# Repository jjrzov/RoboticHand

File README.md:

# ME 507 - Teleoperated Robot Hand
By: Sydney Alexander & Jorge Ramirez

This repository holds all the work done for our Fall 2025 ME 507 mechatronics 
class, Mechanical Control System Design. We chose to do a teleoperated
robot hand for our final project. The robot hand is controlled by a glove
that can be worn by the user. The user has control over each finger and a
palm bending motion on the robot hand.

The repository is split into 3 parts: 
* Mechanical Design Files (<https://github.com/jjrzov/RoboticHand/tree/main/CAD>)
* PCB Files
* Software Files    (<https://github.com/jjrzov/RoboticHand/tree/main/Code>)

More information can be found in the report:
<https://docs.google.com/document/d/1OJhpxcHGqPs-KphNlcnnhu6IluXgC120gNegF1xwxDM/edit?usp=sharing>

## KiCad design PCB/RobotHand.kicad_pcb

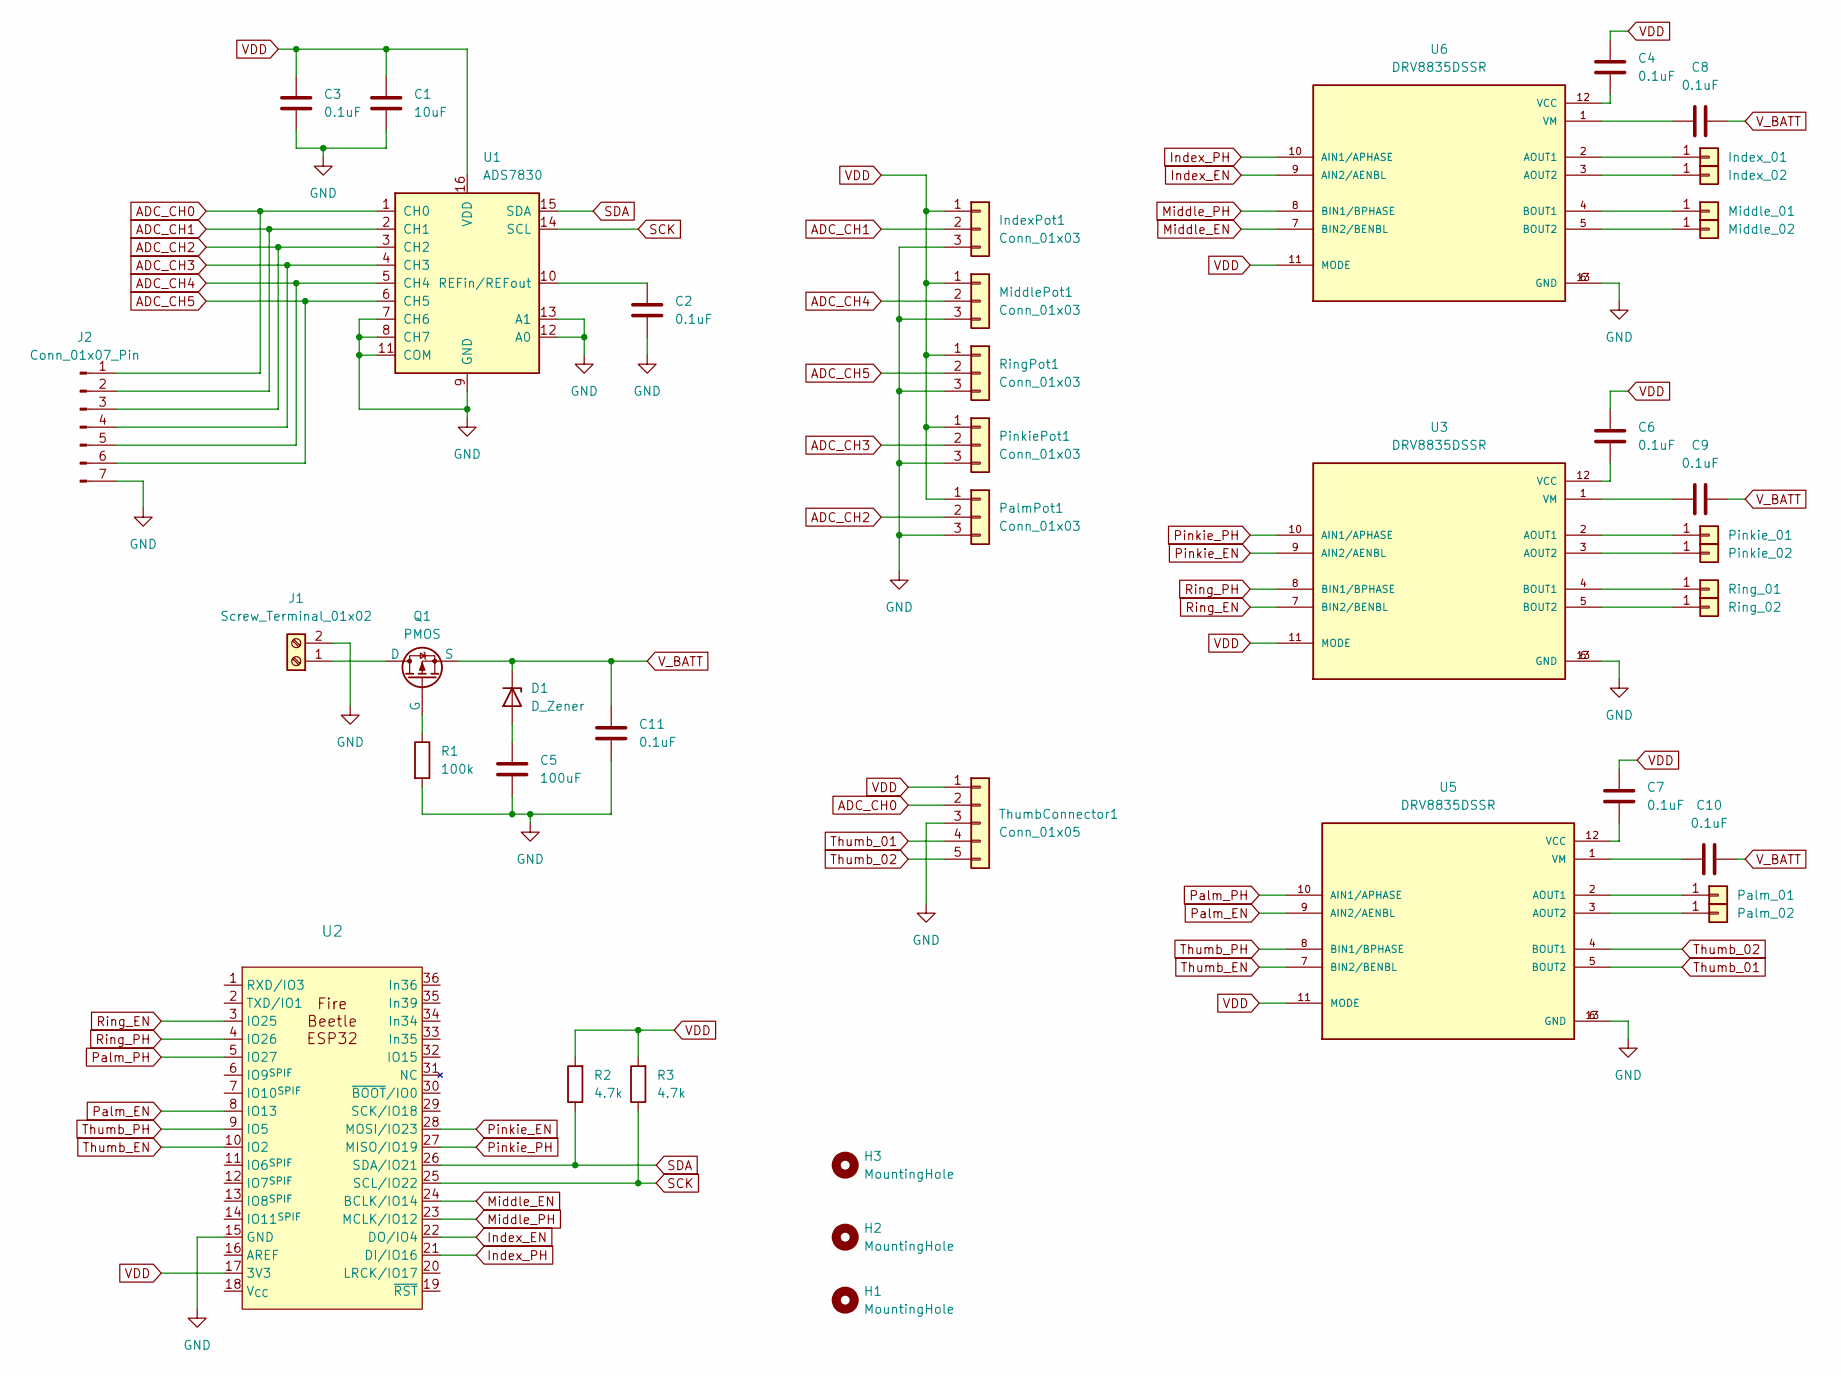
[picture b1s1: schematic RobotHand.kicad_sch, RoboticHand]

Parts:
C1: 10uF; C_0805_2012Metric_Pad1.18x1.45mm_HandSolder
C2, C3, C4, C6, C7, C8, C9, C10, C11: 0.1uF; C_0805_2012Metric_Pad1.18x1.45mm_HandSolder
C5: 100uF; C_0805_2012Metric_Pad1.18x1.45mm_HandSolder
D1: D_Zener; D_SOD-123
H1, H2, H3: MountingHole; MountingHole_6.4mm_M6
IndexPot1: Conn_01x03; PinHeader_1x03_P2.54mm_Vertical
Index_01, Index_02: Conn_01x01; PinHeader_1x01_P2.54mm_Vertical
J1: Screw_Terminal_01x02; TerminalBlock_Xinya_XY308-2.54-2P_1x02_P2.54mm_Horizontal
J2: Conn_01x07_Pin; PinSocket_1x07_P2.54mm_Vertical
MiddlePot1: Conn_01x03; PinHeader_1x03_P2.54mm_Vertical
Middle_01, Middle_02: Conn_01x01; PinHeader_1x01_P2.54mm_Vertical
PalmPot1: Conn_01x03; PinHeader_1x03_P2.54mm_Vertical
Palm_01, Palm_02: Conn_01x01; PinHeader_1x01_P2.54mm_Vertical
PinkiePot1: Conn_01x03; PinHeader_1x03_P2.54mm_Vertical
Pinkie_01, Pinkie_02: Conn_01x01; PinHeader_1x01_P2.54mm_Vertical
Q1: PMOS; SOT-23-3
R1: 100k; R_0805_2012Metric
R2, R3: 4.7k; R_0805_2012Metric
RingPot1: Conn_01x03; PinHeader_1x03_P2.54mm_Vertical
Ring_01, Ring_02: Conn_01x01; PinHeader_1x01_P2.54mm_Vertical
ThumbConnector1: Conn_01x05; PinHeader_1x05_P2.54mm_Vertical
U1: ADS7830; TSSOP-16_4.4x5mm_P0.65mm
U2: FireBeetle-ESP32
U3, U5, U6: DRV8835DSSR; WSON-12-1EP_3x2mm_P0.5mm_EP1x2.65; PARTREV H

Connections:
ADC_CH0: J2.1, ThumbConnector1.2, U1.1 (CH0)
ADC_CH1: IndexPot1.2, J2.2, U1.2 (CH1)
ADC_CH2: J2.3, PalmPot1.2, U1.3 (CH2)
ADC_CH3: J2.4, PinkiePot1.2, U1.4 (CH3)
ADC_CH4: J2.5, MiddlePot1.2, U1.5 (CH4)
ADC_CH5: J2.6, RingPot1.2, U1.6 (CH5)
GND: C1.1, C2.2, C3.2, C5.2, C11.2, IndexPot1.3, J1.2, J2.7, MiddlePot1.3, PalmPot1.3, PinkiePot1.3, R1.2, RingPot1.3, ThumbConnector1.3, U1.7 (CH6), U1.8 (CH7), U1.9 (GND), U1.11 (COM), U1.12 (A0), U1.13 (A1), U2.15 (GND), U3.6 (GND), U3.13 (GND), U5.6 (GND), U5.13 (GND), U6.6 (GND), U6.13 (GND)
Index_EN: U2.22 (DO/IO4), U6.9 (AIN2/AENBL)
Index_PH: U2.21 (DI/IO16), U6.10 (AIN1/APHASE)
Middle_EN: U2.24 (BCLK/IO14), U6.7 (BIN2/BENBL)
Middle_PH: U2.23 (MCLK/IO12), U6.8 (BIN1/BPHASE)
unnamed: C5.1, D1.2 (A)
unnamed: Index_01.1, U6.2 (AOUT1)
unnamed: Index_02.1, U6.3 (AOUT2)
unnamed: J1.1, Q1.1 (D)
unnamed: Middle_01.1, U6.4 (BOUT1)
unnamed: Middle_02.1, U6.5 (BOUT2)
unnamed: Palm_01.1, U5.2 (AOUT1)
unnamed: Palm_02.1, U5.3 (AOUT2)
unnamed: Pinkie_01.1, U3.2 (AOUT1)
unnamed: Pinkie_02.1, U3.3 (AOUT2)
unnamed: Q1.2 (G), R1.1
unnamed: Ring_01.1, U3.4 (BOUT1)
unnamed: Ring_02.1, U3.5 (BOUT2)
unnamed: C2.1, U1.10 (REFin/REFout)
unnamed: C6.1, U3.12 (VCC)
unnamed: C9.1, U3.1 (VM)
unnamed: C7.1, U5.12 (VCC)
unnamed: C10.2, U5.1 (VM)
unnamed: C4.1, U6.12 (VCC)
unnamed: C8.1, U6.1 (VM)
Palm_EN: U2.8 (IO13), U5.9 (AIN2/AENBL)
Palm_PH: U2.5 (IO27), U5.10 (AIN1/APHASE)
Pinkie_EN: U2.28 (MOSI/IO23), U3.9 (AIN2/AENBL)
Pinkie_PH: U2.27 (MISO/IO19), U3.10 (AIN1/APHASE)
Ring_EN: U2.3 (IO25), U3.7 (BIN2/BENBL)
Ring_PH: U2.4 (IO26), U3.8 (BIN1/BPHASE)
SCK: R3.1, U1.14 (SCL), U2.25 (SCL/IO22)
SDA: R2.1, U1.15 (SDA), U2.26 (SDA/IO21)
Thumb_01: ThumbConnector1.4, U5.5 (BOUT2)
Thumb_02: ThumbConnector1.5, U5.4 (BOUT1)
Thumb_EN: U2.10 (IO2), U5.7 (BIN2/BENBL)
Thumb_PH: U2.9 (IO5), U5.8 (BIN1/BPHASE)
VDD: C1.2, C3.1, C4.2, C6.2, C7.2, IndexPot1.1, MiddlePot1.1, PalmPot1.1, PinkiePot1.1, R2.2, R3.2, RingPot1.1, ThumbConnector1.1, U1.16 (VDD), U2.17 (3V3), U3.11 (MODE), U5.11 (MODE), U6.11 (MODE)
V_BATT: C8.2, C9.2, C10.1, C11.1, D1.1 (K), Q1.3 (S)

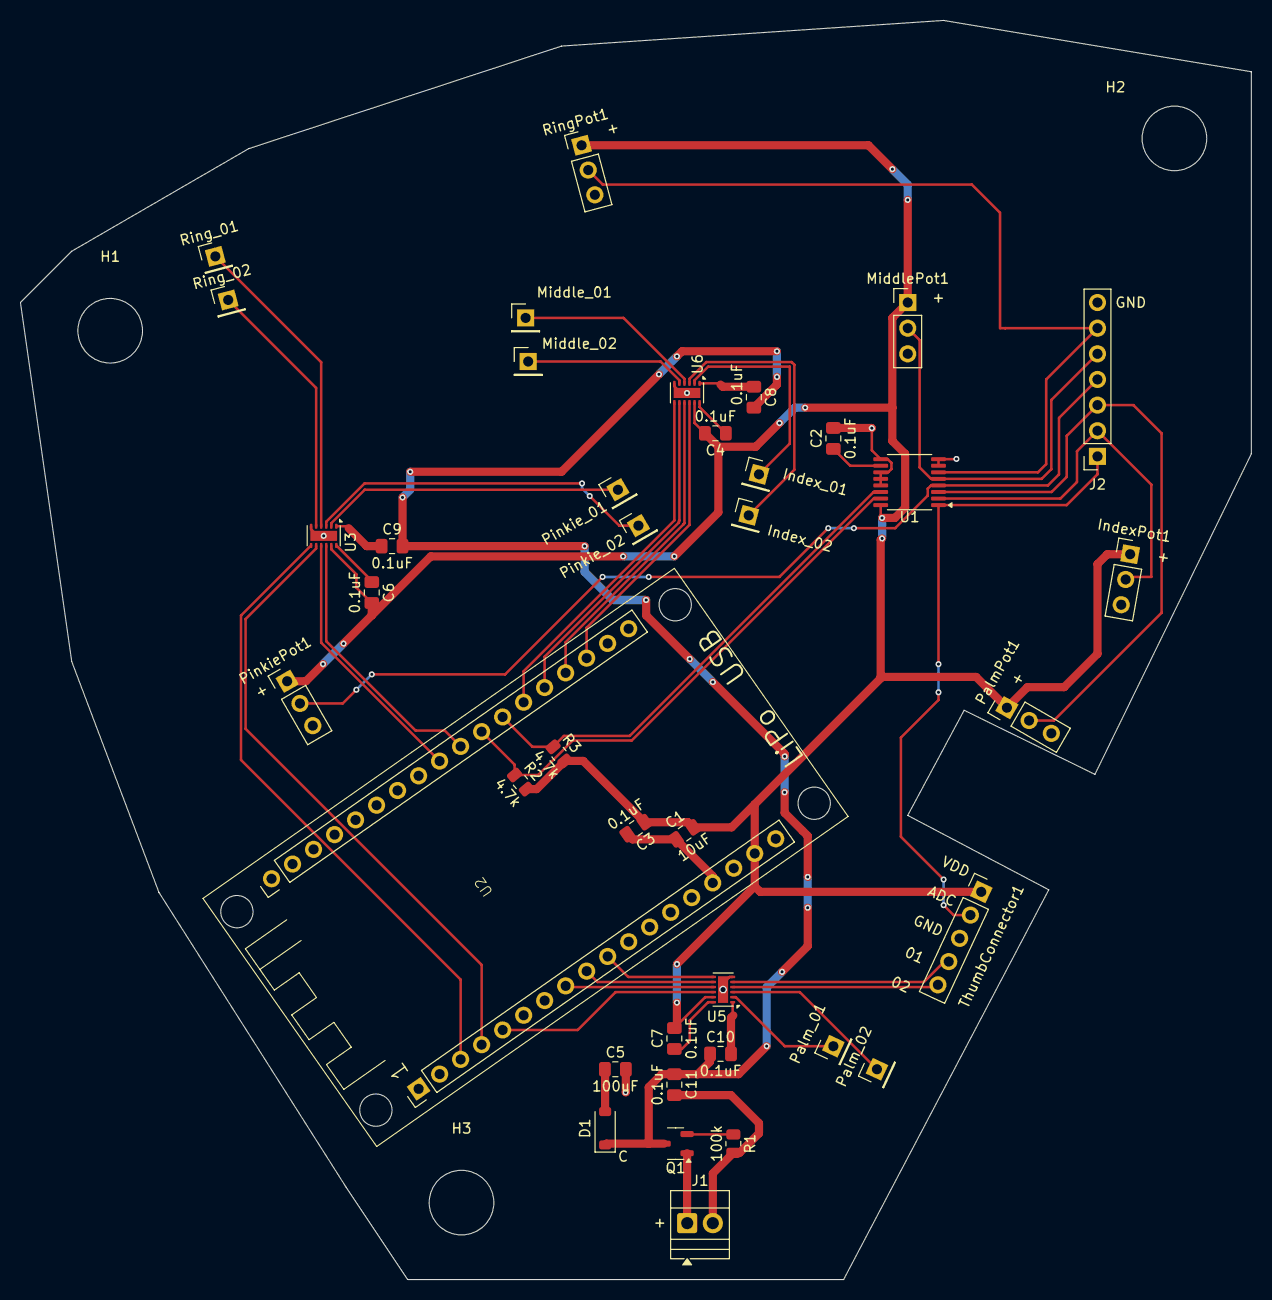
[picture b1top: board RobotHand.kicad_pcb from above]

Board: 2 copper layers, 121.9 x 124.7 mm, 42 parts (0 on the bottom side), 45 nets.

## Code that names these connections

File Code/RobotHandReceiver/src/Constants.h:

/**
 * @file Constants.h
 * @brief Hardware configuration, calibration values, and shared data types.
 *
 * This file centralizes all system-wide constants for:
 *  - External ADC channel mappings
 *  - Motor control parameters
 *  - Homing thresholds and gains
 *  - Flex sensor and encoder calibration
 *  - Shared data structures and state enums
 *
 * All values here are platform- and hardware-specific.
 */

#ifndef CONSTANTS_H
#define CONSTANTS_H

#include <Arduino.h>
#include <Adafruit_ADS7830.h>
#include <esp_now.h>
#include <WiFi.h>

/** @name External ADC channel assignments
 *  @brief ADS7830 channel numbers for each finger encoder.
 *  @{
 */
const uint8_t EXT_ADC_THUMB = 0;
const uint8_t EXT_ADC_INDEX = 1;
const uint8_t EXT_ADC_MIDDLE = 4;
const uint8_t EXT_ADC_RING = 5;
const uint8_t EXT_ADC_PINKIE = 3;
const uint8_t EXT_ADC_PALM = 2;
/** @} */

/** @name Homing control parameters
 *  @brief Gains and thresholds used during finger homing.
 *  @{
 */
const float HOMING_KP = 0.5f;
const uint32_t HOMING_PWM_MIN = 150;
const uint32_t HOMING_PWM_MAX = 800;
const uint32_t HOMING_THRESHOLD = 20;
/** @} */

/** @name Motor PWM configuration
 *  @brief Global PWM parameters shared across all motors.
 *  @{
 */
const int MOTOR_PWM_FREQ = 15000;     // 15kHz PWM Signal
const int MOTOR_PWM_RESOLUTION = 10;  // 10 bit PWM Resolution
/** @} */


/** @name Motor pin and channel mappings
 *  @brief PWM channels, output pins, and phase pins for each motor.
 *  @{
 */
const int THUMB_PWM_CHANNEL = 0;      // LED PWM Channel 0
const int THUMB_PWM_PIN = 2;  // GPIO 5
const int THUMB_PH_PIN = 5;   // GPIO 2

const int INDEX_PWM_CHANNEL = 1;      // LED PWM Channel 1
const int INDEX_PWM_PIN = 4;  // GPIO 4
const int INDEX_PH_PIN = 16;   // GPIO 16

const int MIDDLE_PWM_CHANNEL = 2;      // LED PWM Channel 2
const int MIDDLE_PWM_PIN = 14;  // GPIO 14
const int MIDDLE_PH_PIN = 12;   // GPIO 12

const int RING_PWM_CHANNEL = 3;      // LED PWM Channel 3
const int RING_PWM_PIN = 25;  // GPIO 25
const int RING_PH_PIN = 26;   // GPIO 26

const int PINKIE_PWM_CHANNEL = 4;      // LED PWM Channel 4
const int PINKIE_PWM_PIN = 23;  // GPIO 23
const int PINKIE_PH_PIN = 19;   // GPIO 19

const int PALM_PWM_CHANNEL = 5;      // LED PWM Channel 5
const int PALM_PWM_PIN = 13;  // GPIO 13
const int PALM_PH_PIN = 27;   // GPIO 27
/** @} */


/** @name Flex sensor calibration
 *  @brief Expected flex sensor range corresponding to open/closed hand.
 *  @{
 */
const float F_MIN = 142.0f;   // flex at fully open
const float F_MAX = 1100.0f;   // flex at fully closed
/** @} */

/** @name Encoder calibration
 *  @brief Encoder range corresponding to open/closed hand.
 *  @{
 */
const float E_MIN = 15.0f;     // encoder at fully open
const float E_MAX = 240.0f;   // encoder at fully closed
/** @} */

/**
 * @brief Data packet containing per-finger values.
 *
 * Used for:
 *  - ESP-NOW communication
 *  - Queue-based inter-task data passing
 */
struct Hand_Data {
  uint16_t thumb_data;
  uint16_t index_data;
  uint16_t middle_data;
  uint16_t ring_data;
  uint16_t pinkie_data;
  uint16_t palm_data;
};

/**
 * @brief Container for per-finger FreeRTOS queues.
 *
 * Each queue holds the most recent target encoder value
 * for its corresponding motor.
 */
class Hand_Queues {
    public:
        QueueHandle_t thumb_queue;
        QueueHandle_t index_queue;
        QueueHandle_t middle_queue;
        QueueHandle_t ring_queue;
        QueueHandle_t pinkie_queue;
        QueueHandle_t palm_queue;

        /**
        * @brief Construct a new Hand_Queues object.
        *
        * Initializes all queues with a depth of one element.
        */
        Hand_Queues() {
          thumb_queue = xQueueCreate(1, sizeof(uint16_t));
          index_queue = xQueueCreate(1, sizeof(uint16_t));
          middle_queue = xQueueCreate(1, sizeof(uint16_t));
          ring_queue = xQueueCreate(1, sizeof(uint16_t));
          pinkie_queue = xQueueCreate(1, sizeof(uint16_t));
          palm_queue = xQueueCreate(1, sizeof(uint16_t));
        }
};


/**
 * @brief State machine states for hand controller.
 */
typedef enum {
    HOMING_STATE,
    POSITION_CONTROL_STATE
} HandState;

#endif

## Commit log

2025-10-17 First Revision of PCB Design
2025-10-17 Added footprints to first PCB version
2025-11-11 Version 2 of PCB
2025-12-03 Code with all fingers commented out
2025-12-03 Single finger homing working not normal operation
2025-12-04 One finger working
2025-12-04 Functionality for all fingers done
2025-12-10 Adding READMEs and doxygen comments to transmitter
2025-12-10 Fixed typo
2025-12-10 Updated Receiver README.md
2025-12-10 Added doxygen comments to receiver
2025-12-10 Doxygen docs
2025-12-10 STEP file of PCB
2025-12-10 Rename README to README.md
2025-12-10 fixed transmitter image README.md
2025-12-10 Done with transmitter readme
2025-12-10 Fixing READMEs
2025-12-10 Finished receiver readme
2025-12-10 Fixed docs
2025-12-10 Added link to CAD README
